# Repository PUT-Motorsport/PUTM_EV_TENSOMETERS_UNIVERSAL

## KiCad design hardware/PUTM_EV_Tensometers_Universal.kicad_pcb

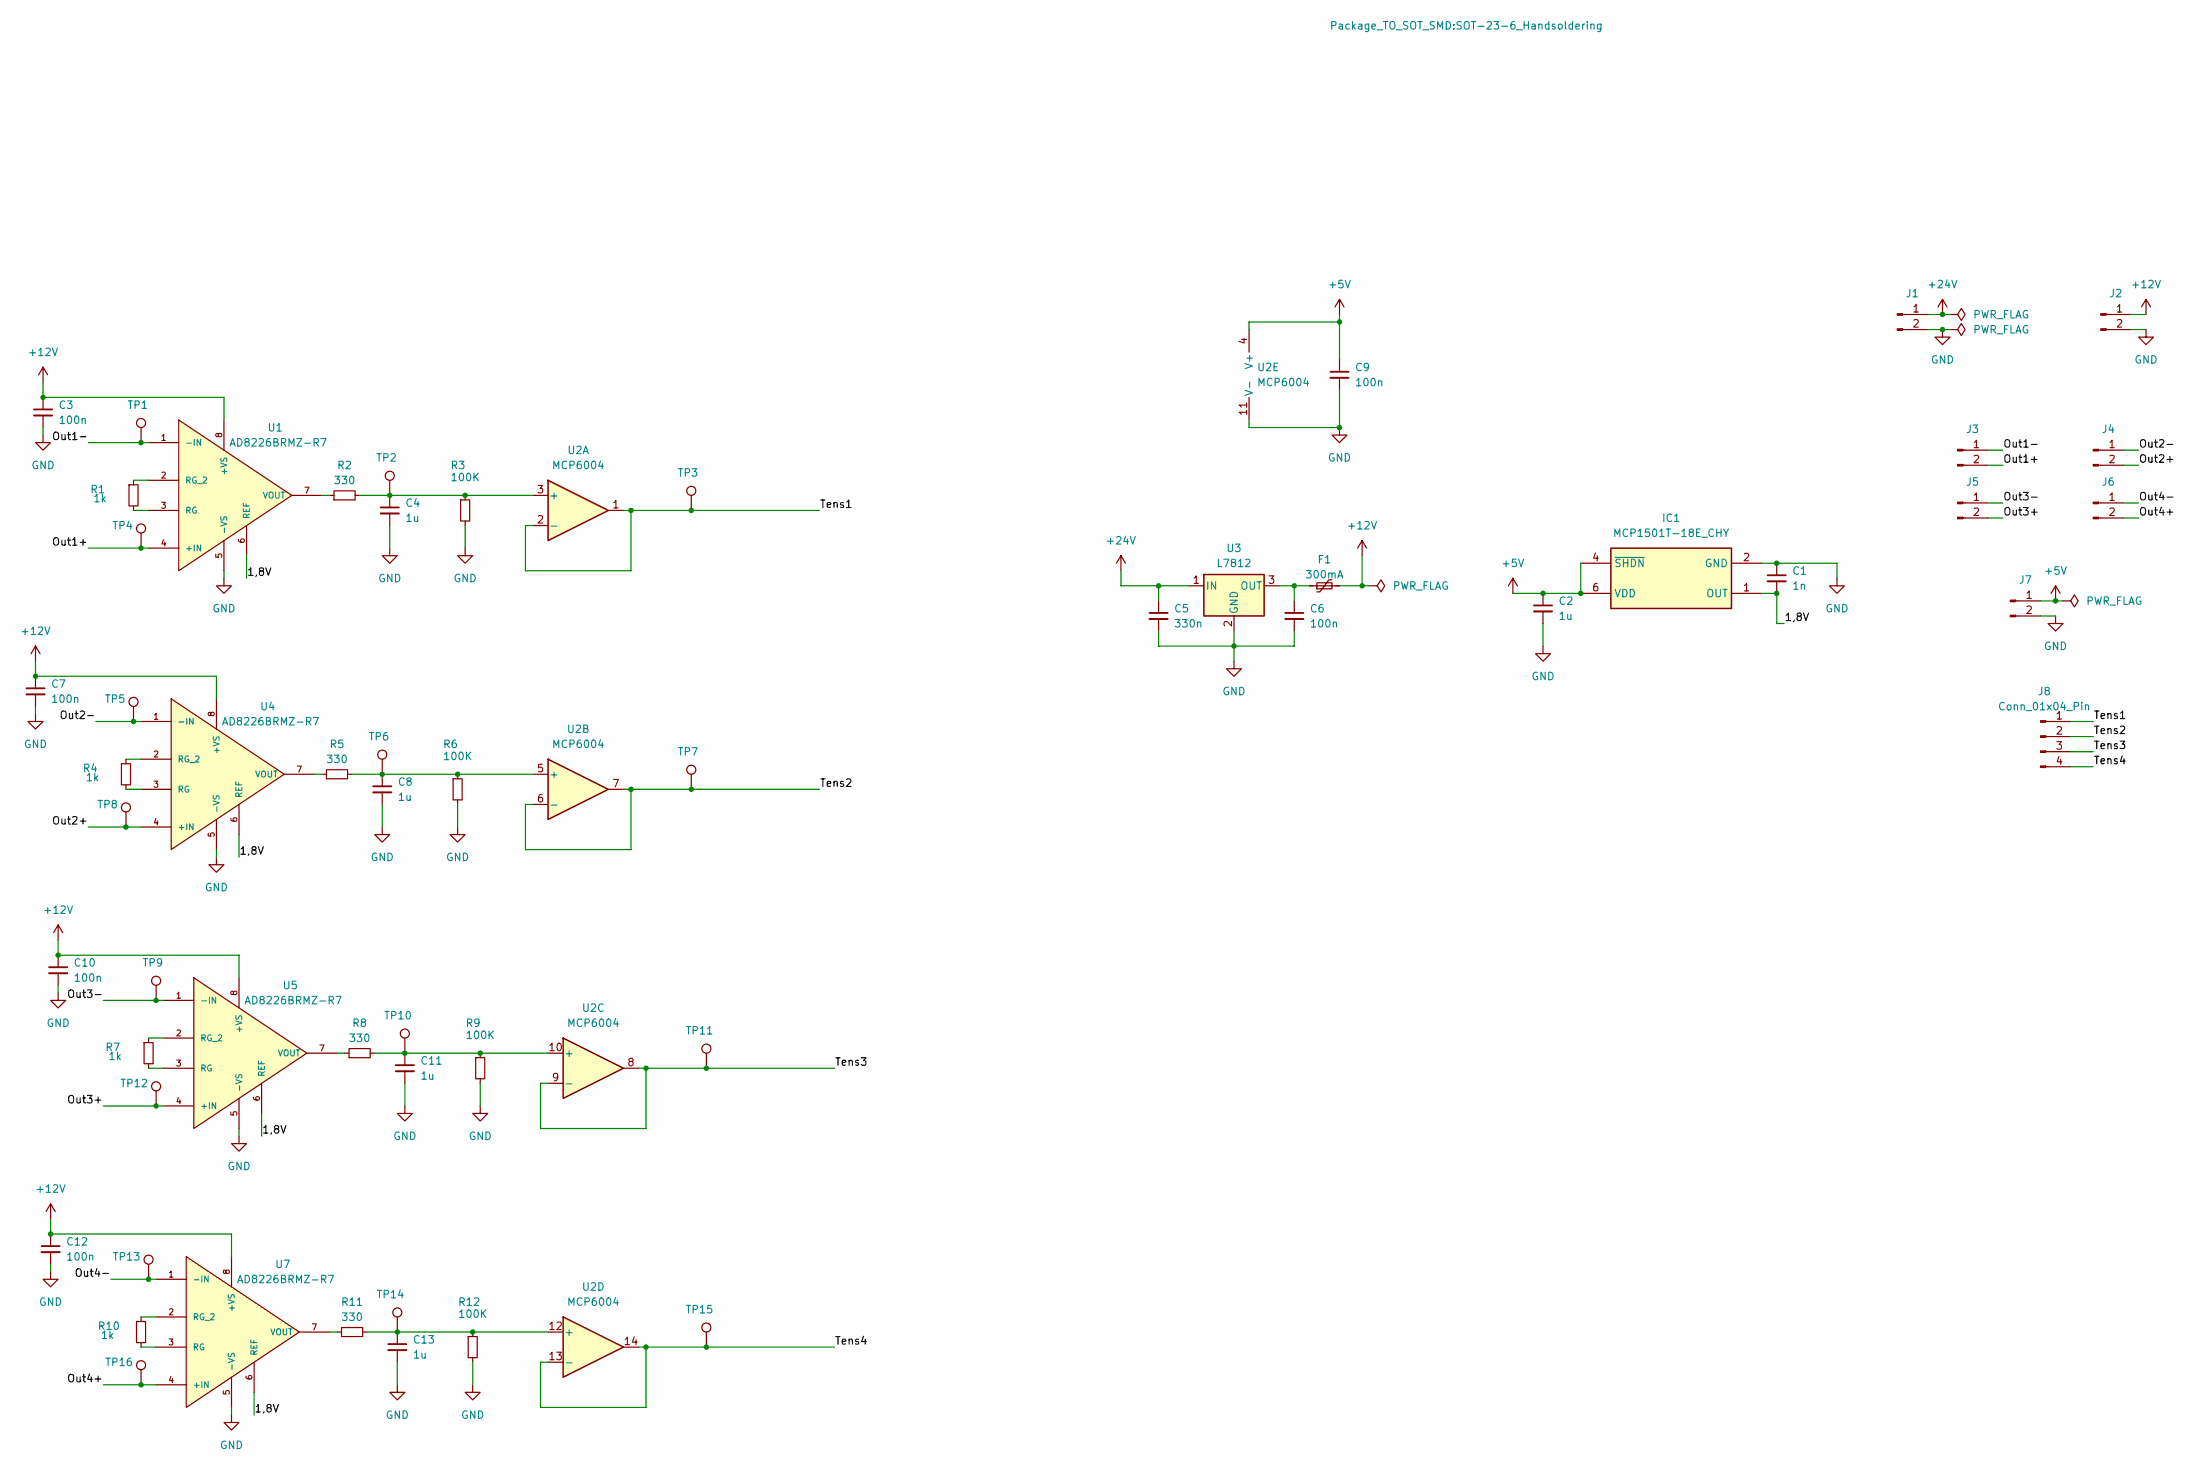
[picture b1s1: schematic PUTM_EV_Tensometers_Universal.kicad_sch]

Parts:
C1: 1n; C_0603_1608Metric
C2, C4, C8, C11, C13: 1u; C_0603_1608Metric
C3, C6, C7, C9, C10, C12: 100n; C_0603_1608Metric
C5: 330n; C_0603_1608Metric
F1: 300mA; Fuse_0603_1608Metric_Pad1.05x0.95mm_HandSolder; Mouser Part Number 603-SMD0603B010TF
IC1: MCP1501T-18E_CHY; SOT-23-6_Handsoldering; Manufacturer_Part_Number MCP1501T-18E/CHY; Mouser Part Number 579-MCP1501T-18E/CHY
J1, J2, J3, J4, J5, J6, J7: Conn_01x02_Pin; SolderWire-0.25sqmm_1x02_P4.2mm_D0.65mm_OD1.7mm_Relief
J8: Conn_01x04_Pin; SolderWire-0.25sqmm_1x04_P4.2mm_D0.65mm_OD1.7mm_Relief
R1, R4, R7, R10: 1k; R_0603_1608Metric
R2, R5, R8, R11: 330; R_0603_1608Metric
R3, R6, R9, R12: 100K; R_0603_1608Metric
TP1, TP2, TP3, TP4, TP5, TP6, TP7, TP8, TP9, TP10, TP11, TP12, TP13, TP14, TP15, TP16: BR_N; TestPoint_Pad_D1.0mm
U1, U4, U5, U7: AD8226BRMZ-R7; MSOP-8_3x3mm_P0.65mm; MPN AD8226BRMZ-R7
U2: MCP6004; SOIC-14_3.9x8.7mm_P1.27mm
U3: L7812; TO-263-2

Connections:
+5V: C2.1, C9.1, IC1.4 (~SHDN), IC1.6 (VDD), J7.1, U2.4 (V+)
+12V: C3.1, C7.1, C10.1, C12.1, F1.2, J2.1, U1.8 (+VS), U4.8 (+VS), U5.8 (+VS), U7.8 (+VS)
+24V: C5.1, J1.1, U3.1 (IN)
/1,8V: C1.2, IC1.1 (OUT), U1.6 (REF), U4.6 (REF), U5.6 (REF), U7.6 (REF)
/Out1+: J3.2, TP4.1 (1_1), U1.4 (+IN)
/Out1-: J3.1, TP1.1 (1_1), U1.1 (-IN)
/Out2+: J4.2, TP8.1 (1_1), U4.4 (+IN)
/Out2-: J4.1, TP5.1 (1_1), U4.1 (-IN)
/Out3+: J5.2, TP12.1 (1_1), U5.4 (+IN)
/Out3-: J5.1, TP9.1 (1_1), U5.1 (-IN)
/Out4+: J6.2, TP16.1 (1_1), U7.4 (+IN)
/Out4-: J6.1, TP13.1 (1_1), U7.1 (-IN)
/Tens1: J8.1, TP3.1 (1_1), U2.1, U2.2 (-)
/Tens2: J8.2, TP7.1 (1_1), U2.6 (-), U2.7
/Tens3: J8.3, TP11.1 (1_1), U2.8, U2.9 (-)
/Tens4: J8.4, TP15.1 (1_1), U2.13 (-), U2.14
GND: C1.1, C2.2, C3.2, C4.2, C5.2, C6.2, C7.2, C8.2, C9.2, C10.2, C11.2, C12.2, C13.2, IC1.2 (GND), IC1.3 (GND_2), IC1.5 (GND_3), J1.2, J2.2, J7.2, R3.2, R6.2, R9.2, R12.2, U1.5 (-VS), U2.11 (V-), U3.2 (GND), U4.5 (-VS), U5.5 (-VS), U7.5 (-VS)
unnamed: R1.2, U1.3 (RG)
unnamed: R1.1, U1.2 (RG_2)
unnamed: R2.1, U1.7 (VOUT)
unnamed: C4.1, R2.2, R3.1, TP2.1 (1_1), U2.3 (+)
unnamed: C8.1, R5.2, R6.1, TP6.1 (1_1), U2.5 (+)
unnamed: C11.1, R8.2, R9.1, TP10.1 (1_1), U2.10 (+)
unnamed: C13.1, R11.2, R12.1, TP14.1 (1_1), U2.12 (+)
unnamed: C6.1, F1.1, U3.3 (OUT)
unnamed: R4.2, U4.3 (RG)
unnamed: R4.1, U4.2 (RG_2)
unnamed: R5.1, U4.7 (VOUT)
unnamed: R7.2, U5.3 (RG)
unnamed: R7.1, U5.2 (RG_2)
unnamed: R8.1, U5.7 (VOUT)
unnamed: R10.2, U7.3 (RG)
unnamed: R10.1, U7.2 (RG_2)
unnamed: R11.1, U7.7 (VOUT)

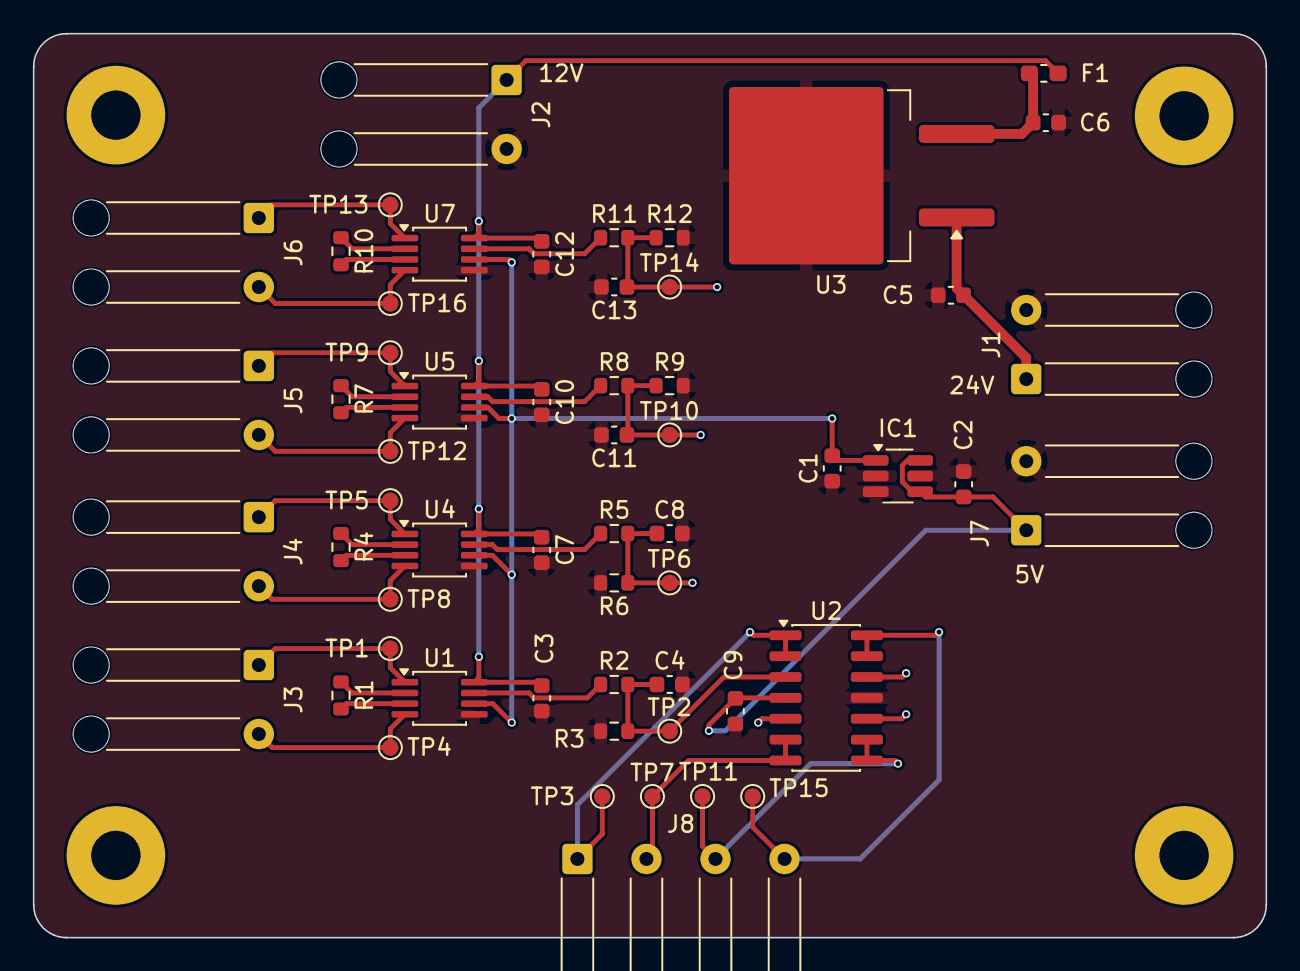
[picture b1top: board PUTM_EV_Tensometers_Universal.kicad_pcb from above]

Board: 4 copper layers, 75.0 x 55.0 mm, 57 parts (0 on the bottom side), 34 nets.
